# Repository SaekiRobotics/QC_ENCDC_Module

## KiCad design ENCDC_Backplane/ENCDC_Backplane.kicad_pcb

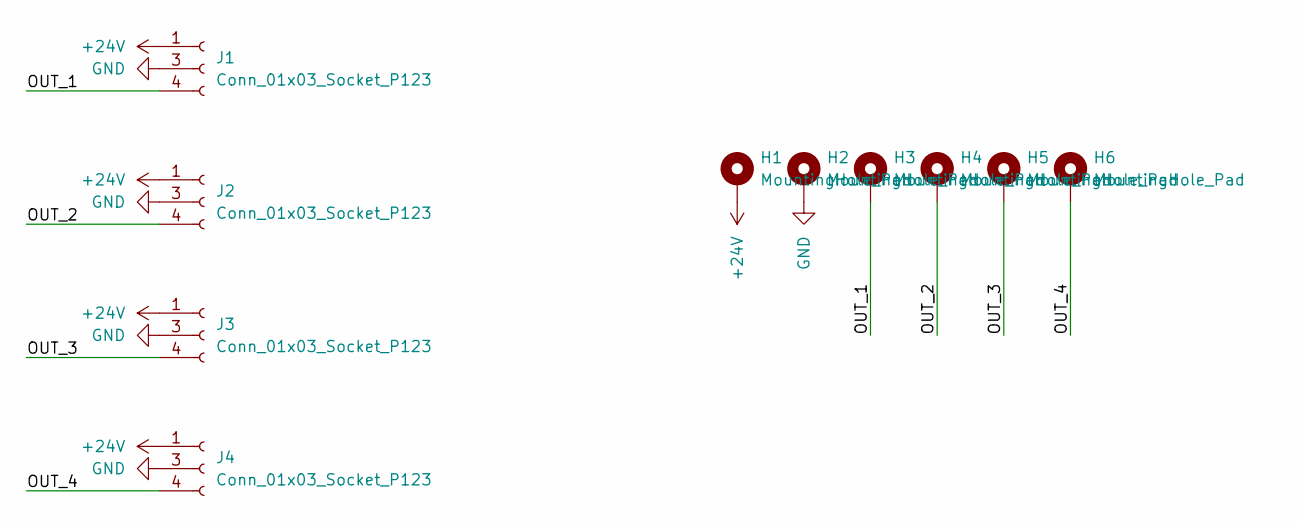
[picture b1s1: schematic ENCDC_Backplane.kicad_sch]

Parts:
H1, H2, H3, H4, H5, H6: MountingHole_Pad; MountingHole_2.2mm_M2_DIN965_Pad
J1, J2, J3, J4: Conn_01x03_Socket_P123; CONN3_T4043014031-000_TEC

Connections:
+24V: H1.1, J1.1, J2.1, J3.1, J4.1
/OUT_1: H3.1, J1.4
/OUT_2: H4.1, J2.4
/OUT_3: H5.1, J3.4
/OUT_4: H6.1, J4.4
GND: H2.1, J1.3, J2.3, J3.3, J4.3

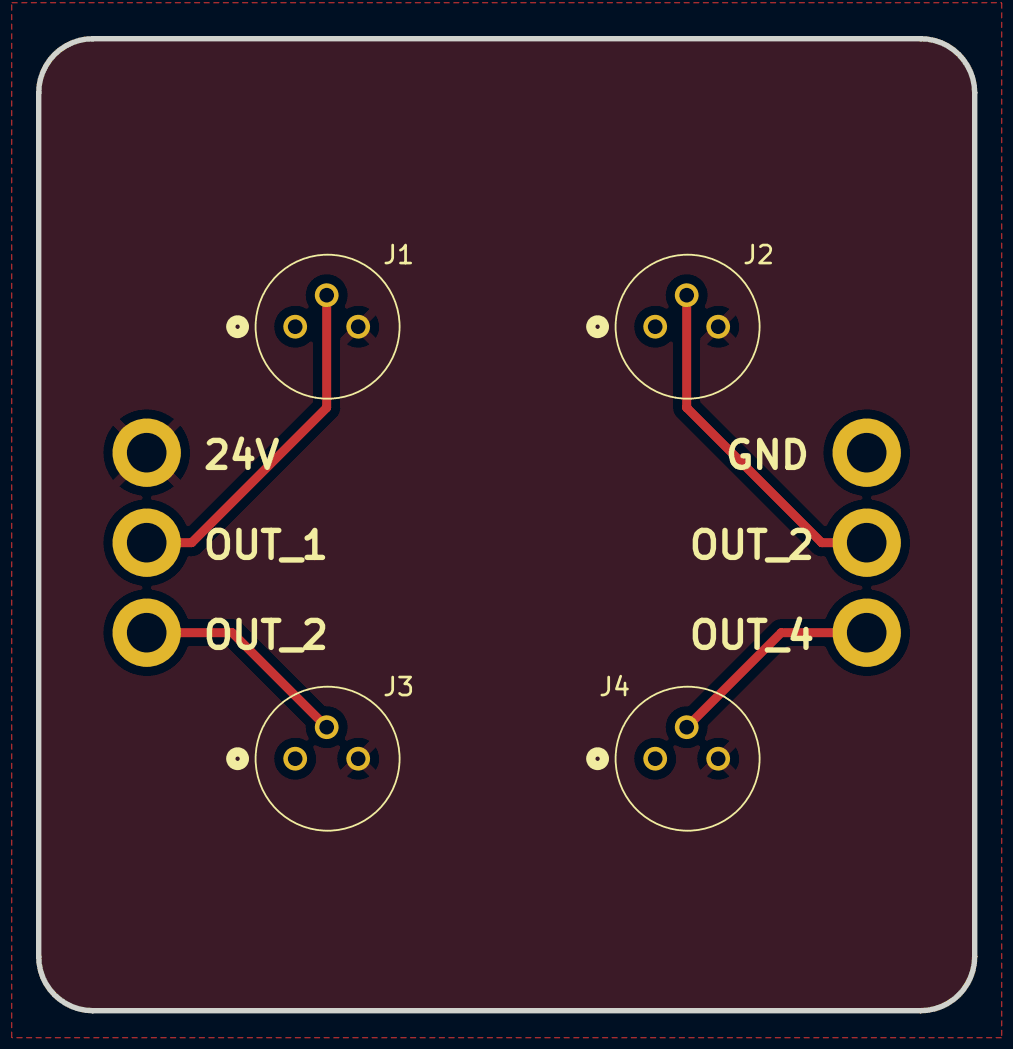
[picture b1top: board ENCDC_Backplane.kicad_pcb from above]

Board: 2 copper layers, 52.0 x 54.0 mm, 10 parts (0 on the bottom side), 6 nets.

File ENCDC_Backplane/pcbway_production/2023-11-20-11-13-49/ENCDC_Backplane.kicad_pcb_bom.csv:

designator,quantity,value,pack,mpn,mount_type
"H1, H2, H3, H4, H5, H6",6,MountingHole_Pad,MountingHole_2.2mm_M2_DIN965_Pad,,tht
"J1, J2, J3, J4",4,Conn_01x03_Socket_P123,CONN3_T4043014031-000_TEC,,tht

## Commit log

2023-11-20 Layout done
2023-11-21 Added manufacturing files
